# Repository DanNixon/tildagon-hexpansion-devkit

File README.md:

# Tildagon Hexpansion dev kit

A basic, quick and dirty development kit for hexpansions for the [Tildagon](https://tildagon.badge.emfcamp.org/) badge.

Accurately replicates i2c and low speed IO/LED drivers of ports D, E and F from the actual badge, with breakouts for the entire expansion port.
i2c is as per the actual badge, with the AW9523B connected to port 7 of the TCA9548A.
Default address configuration of both the AW9523B and TCA9548A match what is used on the badge (so you should not have to adjust the solder jumpers).

Paired with your ESP32-S3 dev board of choice, this should allow you to develop something more than "shape with LED" hexpansions prior to EMF 2024.

## Pinouts

"Pin" refers to the index used on the Tildagon design files.
"Letter" refers to the letter assigned to the pins in the Hexpansion example.
Why the two different pin identification schemes exist is a mystery to me...

### Low Speed

| Pin | Letter | Port D | Port E | Port F |
|-----|--------|--------|--------|--------|
| 1   | A      | 1.0    | 0.2    | 0.7    |
| 2   | B      | 1.1    | 0.3    | 1.4    |
| 3   | C      | 1.2    | 0.4    | 1.5    |
| 4   | D      | 1.3    | 0.5    | 1.6    |
| 5   | E      | 0.0    | 0.6    | 1.7    |

### High Speed

| Pin | Letter |
|-----|--------|
| 1   | F      |
| 2   | G      |
| 3   | H      |
| 4   | I      |

### i2c

| Bus | Port |
|-----|------|
| 4   | D    |
| 5   | E    |
| 6   | F    |
| 7   | sys  |

## See also

- [badge-2024-hardware](https://github.com/emfcamp/badge-2024-hardware)
- [TCA9548A datasheet](https://www.ti.com/lit/ds/symlink/tca9548a.pdf)
- [AW9523B datasheet](https://cdn-shop.adafruit.com/product-files/4886/AW9523+English+Datasheet.pdf)
- [Hexpansion developer guide](https://tildagon.badge.emfcamp.org/technical-reference/hexpansions/)

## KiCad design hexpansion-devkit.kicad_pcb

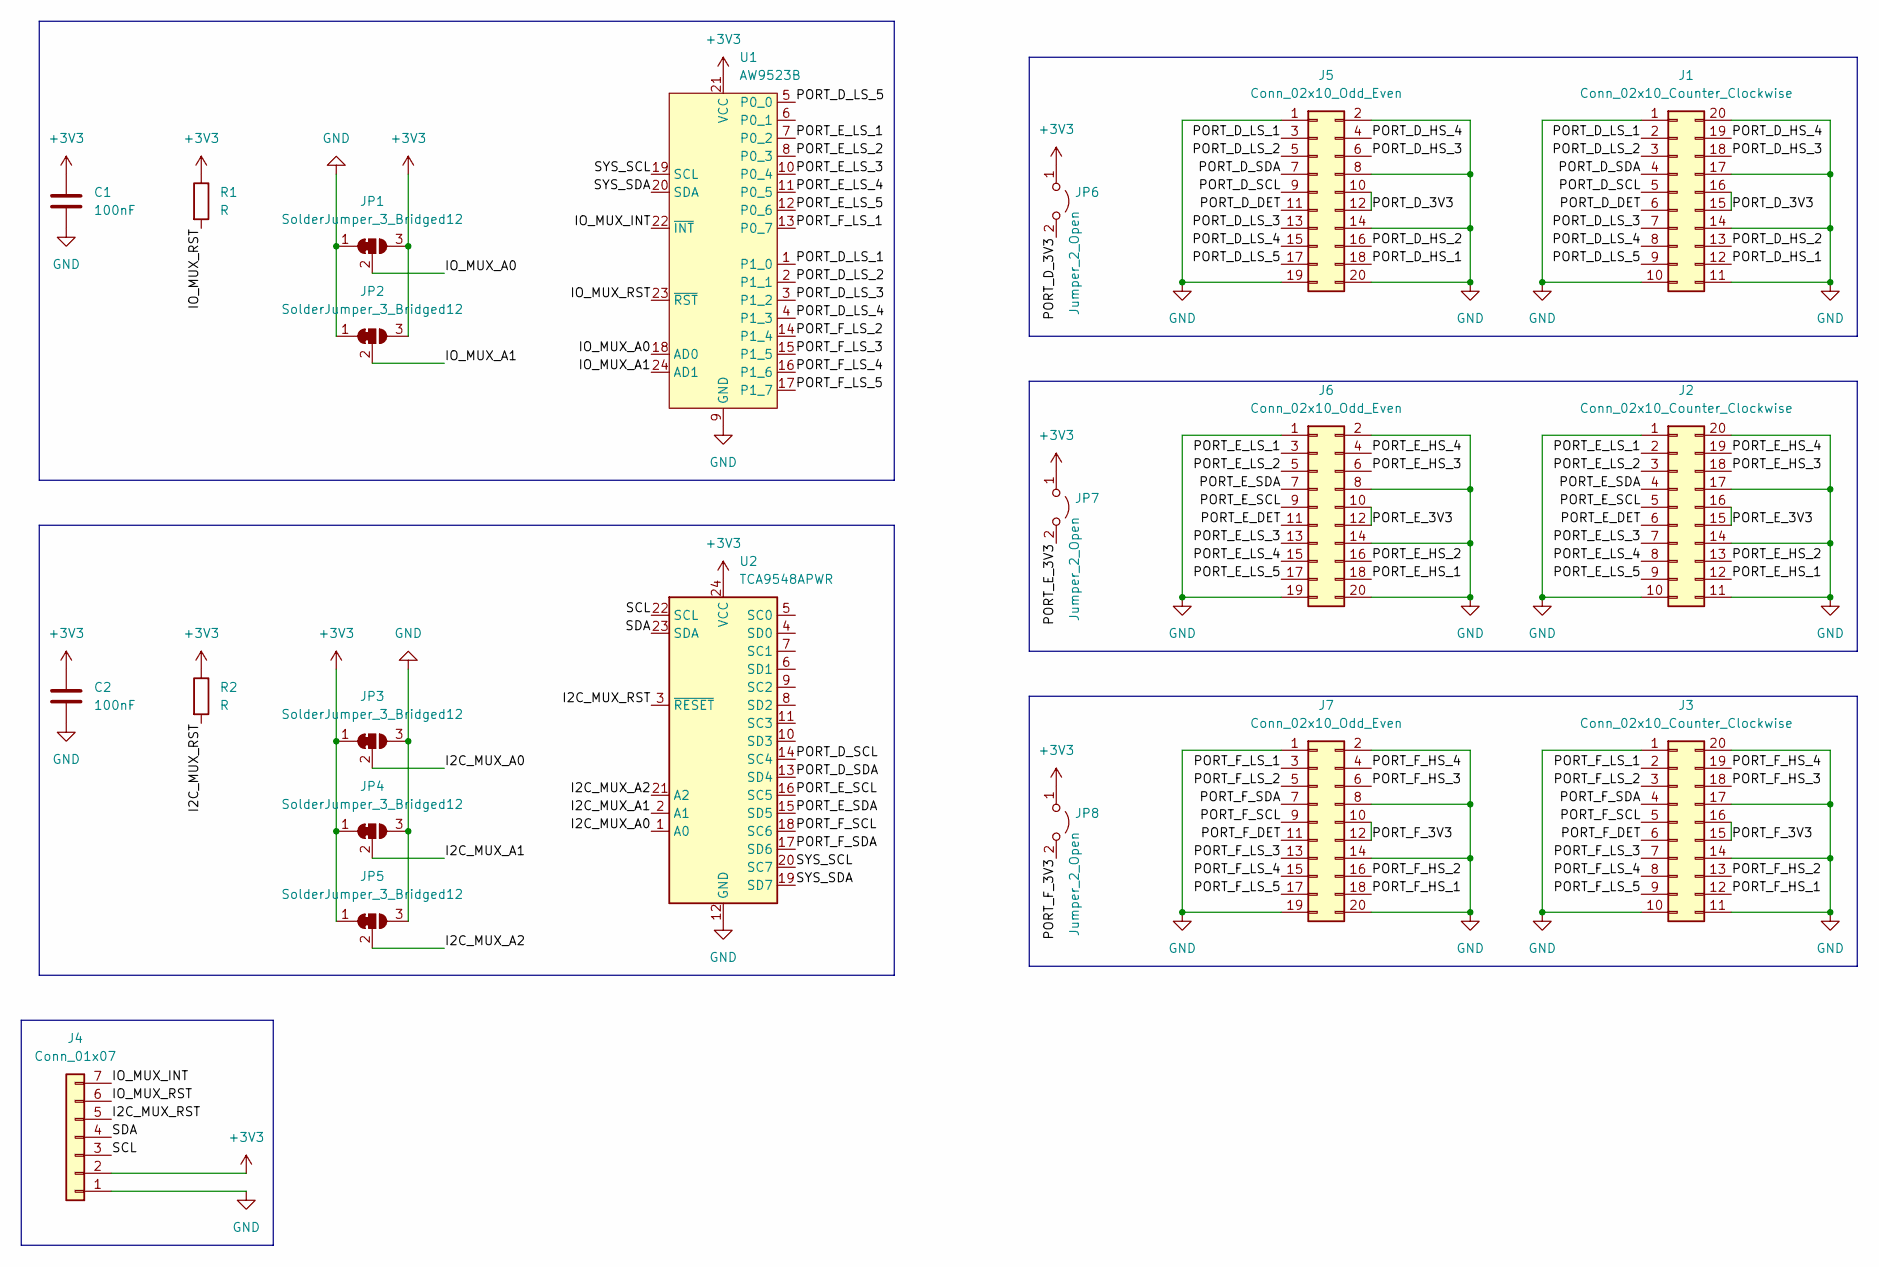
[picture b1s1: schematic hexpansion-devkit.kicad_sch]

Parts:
C1, C2: 100nF; C_0603_1608Metric; LCSC C497032
J1, J2, J3: Conn_02x10_Counter_Clockwise; SFP; LCSC C2897291
J4: Conn_01x07; PinHeader_1x07_P2.54mm_Vertical
J5, J6, J7: Conn_02x10_Odd_Even; PinHeader_2x10_P2.54mm_Vertical
JP1, JP2, JP3, JP4, JP5: SolderJumper_3_Bridged12; SolderJumper-3_P1.3mm_Bridged12_RoundedPad1.0x1.5mm
JP6, JP7, JP8: Jumper_2_Open; TestPoint_2Pads_Pitch2.54mm_Drill0.8mm
R1, R2: R; R_0603_1608Metric; LCSC C2907127
U1: AW9523B; QFN-24-1EP_4x4mm_P0.5mm_EP2.7x2.6mm; LCSC C148077
U2: TCA9548APWR; TSSOP-24_4.4x7.8mm_P0.65mm; LCSC C130026

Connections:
+3V3: C1.1, C2.1, J4.2, JP1.3 (B), JP2.3 (B), JP3.1 (A), JP4.1 (A), JP5.1 (A), JP6.1 (A), JP7.1 (A), JP8.1 (A), R1.1, R2.1, U1.21 (VCC), U2.24 (VCC)
/I2C_MUX_A0: JP3.2 (C), U2.1 (A0)
/I2C_MUX_A1: JP4.2 (C), U2.2 (A1)
/I2C_MUX_A2: JP5.2 (C), U2.21 (A2)
/I2C_MUX_RST: J4.5, R2.2, U2.3 (~RESET)
/IO_MUX_A0: JP1.2 (C), U1.18 (AD0)
/IO_MUX_A1: JP2.2 (C), U1.24 (AD1)
/IO_MUX_INT: J4.7, U1.22 (~INT)
/IO_MUX_RST: J4.6, R1.2, U1.23 (~RST)
/PORT_D_3V3: J1.15, J1.16, J5.10, J5.12, JP6.2 (B)
/PORT_D_DET: J1.6, J5.11
/PORT_D_HS_1: J1.12, J5.18
/PORT_D_HS_2: J1.13, J5.16
/PORT_D_HS_3: J1.18, J5.6
/PORT_D_HS_4: J1.19, J5.4
/PORT_D_LS_1: J1.2, J5.3, U1.1 (P1_0)
/PORT_D_LS_2: J1.3, J5.5, U1.2 (P1_1)
/PORT_D_LS_3: J1.7, J5.13, U1.3 (P1_2)
/PORT_D_LS_4: J1.8, J5.15, U1.4 (P1_3)
/PORT_D_LS_5: J1.9, J5.17, U1.5 (P0_0)
/PORT_D_SCL: J1.5, J5.9, U2.14 (SC4)
/PORT_D_SDA: J1.4, J5.7, U2.13 (SD4)
/PORT_E_3V3: J2.15, J2.16, J6.10, J6.12, JP7.2 (B)
/PORT_E_DET: J2.6, J6.11
/PORT_E_HS_1: J2.12, J6.18
/PORT_E_HS_2: J2.13, J6.16
/PORT_E_HS_3: J2.18, J6.6
/PORT_E_HS_4: J2.19, J6.4
/PORT_E_LS_1: J2.2, J6.3, U1.7 (P0_2)
/PORT_E_LS_2: J2.3, J6.5, U1.8 (P0_3)
/PORT_E_LS_3: J2.7, J6.13, U1.10 (P0_4)
/PORT_E_LS_4: J2.8, J6.15, U1.11 (P0_5)
/PORT_E_LS_5: J2.9, J6.17, U1.12 (P0_6)
/PORT_E_SCL: J2.5, J6.9, U2.16 (SC5)
/PORT_E_SDA: J2.4, J6.7, U2.15 (SD5)
/PORT_F_3V3: J3.15, J3.16, J7.10, J7.12, JP8.2 (B)
/PORT_F_DET: J3.6, J7.11
/PORT_F_HS_1: J3.12, J7.18
/PORT_F_HS_2: J3.13, J7.16
/PORT_F_HS_3: J3.18, J7.6
/PORT_F_HS_4: J3.19, J7.4
/PORT_F_LS_1: J3.2, J7.3, U1.13 (P0_7)
/PORT_F_LS_2: J3.3, J7.5, U1.14 (P1_4)
/PORT_F_LS_3: J3.7, J7.13, U1.15 (P1_5)
/PORT_F_LS_4: J3.8, J7.15, U1.16 (P1_6)
/PORT_F_LS_5: J3.9, J7.17, U1.17 (P1_7)
/PORT_F_SCL: J3.5, J7.9, U2.18 (SC6)
/PORT_F_SDA: J3.4, J7.7, U2.17 (SD6)
/SCL: J4.3, U2.22 (SCL)
/SDA: J4.4, U2.23 (SDA)
/SYS_SCL: U1.19 (SCL), U2.20 (SC7)
/SYS_SDA: U1.20 (SDA), U2.19 (SD7)
GND: C1.2, C2.2, J1.1, J1.10, J1.11, J1.14, J1.17, J1.20, J2.1, J2.10, J2.11, J2.14, J2.17, J2.20, J3.1, J3.10, J3.11, J3.14, J3.17, J3.20, J4.1, J5.1, J5.2, J5.8, J5.14, J5.19, J5.20, J6.1, J6.2, J6.8, J6.14, J6.19, J6.20, J7.1, J7.2, J7.8, J7.14, J7.19, J7.20, JP1.1 (A), JP2.1 (A), JP3.3 (B), JP4.3 (B), JP5.3 (B), U1.9 (GND), U1.25 (GND), U2.12 (GND)

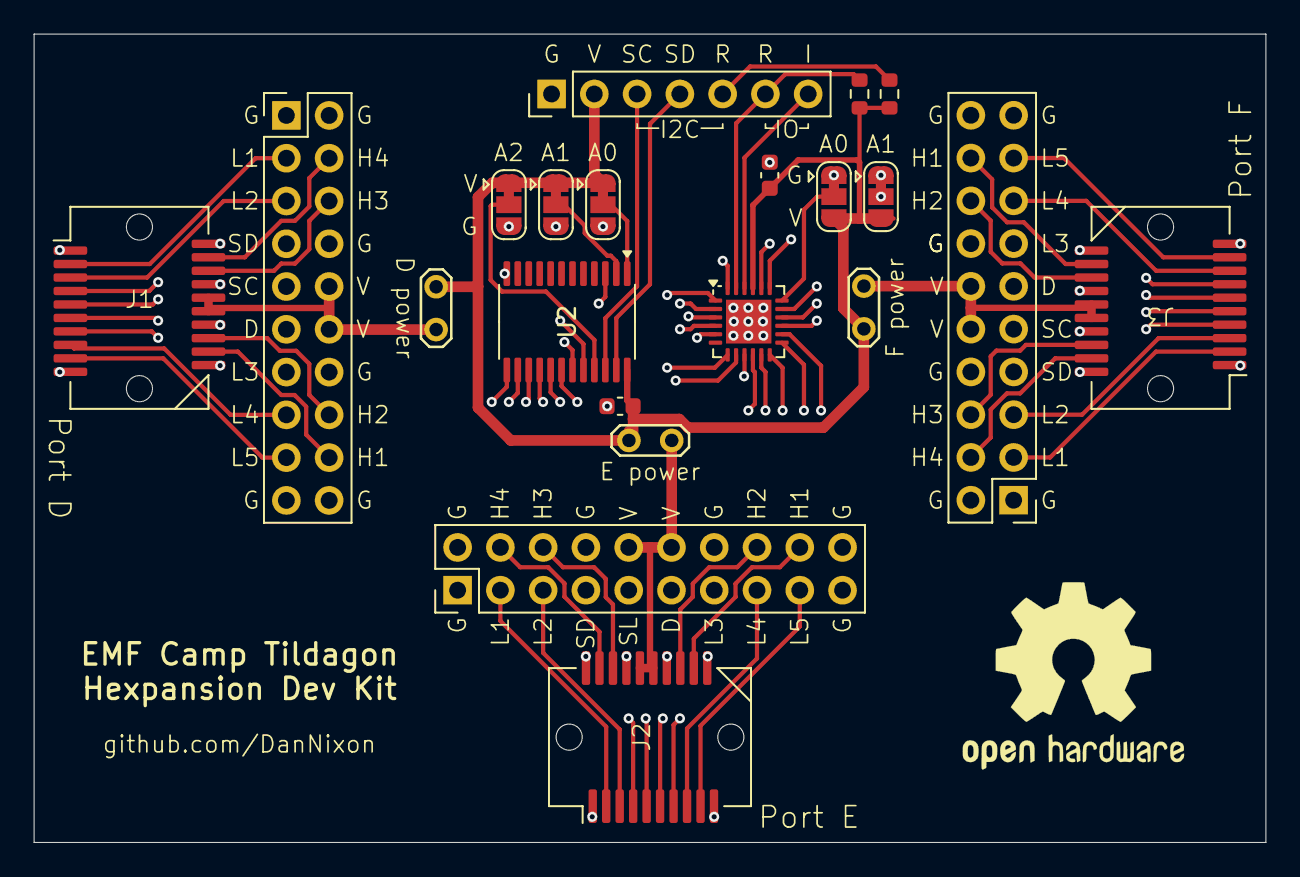
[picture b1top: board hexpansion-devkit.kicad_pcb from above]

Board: 4 copper layers, 73.2 x 48.0 mm, 21 parts (0 on the bottom side), 53 nets.

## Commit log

2024-03-25 Revision 1
2024-04-03 Revision 2
2024-04-03 Move PCB files to subdir
2024-04-03 Test programs
2024-04-03 Flake, formatting and CI
2024-04-03 Docs
2024-04-03 Remove stray notes
2024-04-08 Tidy PCB silkscreen, add new render
2024-04-22 Add FUNDING.yml
2024-04-29 Add pinouts
2024-04-29 Test program for rabbit, blue duck and MS badge hexpansions
2024-05-01 Add MS hexpansion breathe effect
2024-05-13 Bump DeterminateSystems/nix-installer-action from 10 to 11
    Bumps [DeterminateSystems/nix-installer-action](https://github.com/determinatesystems/nix-installer-action) from 10 to 11.
    - [Release notes](https://github.com/determinatesystems/nix-installer-action/releases)
    - [Commits](https://github.com/determinatesystems/nix-installer-action/compare/v10...v11)
    ---
    updated-dependencies:
    - dependency-name: DeterminateSystems/nix-installer-action
2024-05-14 More Maker Space M testing
2024-06-10 Bump DeterminateSystems/nix-installer-action from 11 to 12
    Bumps [DeterminateSystems/nix-installer-action](https://github.com/determinatesystems/nix-installer-action) from 11 to 12.
    - [Release notes](https://github.com/determinatesystems/nix-installer-action/releases)
    - [Commits](https://github.com/determinatesystems/nix-installer-action/compare/v11...v12)
    ---
    updated-dependencies:
    - dependency-name: DeterminateSystems/nix-installer-action
2024-07-29 Bump DeterminateSystems/nix-installer-action from 12 to 13
    Bumps [DeterminateSystems/nix-installer-action](https://github.com/determinatesystems/nix-installer-action) from 12 to 13.
    - [Release notes](https://github.com/determinatesystems/nix-installer-action/releases)
    - [Commits](https://github.com/determinatesystems/nix-installer-action/compare/v12...v13)
    ---
    updated-dependencies:
    - dependency-name: DeterminateSystems/nix-installer-action
2024-09-16 Bump DeterminateSystems/nix-installer-action from 13 to 14
    Bumps [DeterminateSystems/nix-installer-action](https://github.com/determinatesystems/nix-installer-action) from 13 to 14.
    - [Release notes](https://github.com/determinatesystems/nix-installer-action/releases)
    - [Commits](https://github.com/determinatesystems/nix-installer-action/compare/v13...v14)
    ---
    updated-dependencies:
    - dependency-name: DeterminateSystems/nix-installer-action
2024-11-11 Bump DeterminateSystems/nix-installer-action from 14 to 15
    Bumps [DeterminateSystems/nix-installer-action](https://github.com/determinatesystems/nix-installer-action) from 14 to 15.
    - [Release notes](https://github.com/determinatesystems/nix-installer-action/releases)
    - [Commits](https://github.com/determinatesystems/nix-installer-action/compare/v14...v15)
    ---
    updated-dependencies:
    - dependency-name: DeterminateSystems/nix-installer-action
2024-11-18 Bump DeterminateSystems/nix-installer-action from 15 to 16
    Bumps [DeterminateSystems/nix-installer-action](https://github.com/determinatesystems/nix-installer-action) from 15 to 16.
    - [Release notes](https://github.com/determinatesystems/nix-installer-action/releases)
    - [Commits](https://github.com/determinatesystems/nix-installer-action/compare/v15...v16)
    ---
    updated-dependencies:
    - dependency-name: DeterminateSystems/nix-installer-action
2025-04-28 Bump DeterminateSystems/nix-installer-action from 16 to 17
    Bumps [DeterminateSystems/nix-installer-action](https://github.com/determinatesystems/nix-installer-action) from 16 to 17.
    - [Release notes](https://github.com/determinatesystems/nix-installer-action/releases)
    - [Commits](https://github.com/determinatesystems/nix-installer-action/compare/v16...v17)
    ---
    updated-dependencies:
    - dependency-name: DeterminateSystems/nix-installer-action
2025-07-07 Bump DeterminateSystems/nix-installer-action from 17 to 18
    Bumps [DeterminateSystems/nix-installer-action](https://github.com/determinatesystems/nix-installer-action) from 17 to 18.
    - [Release notes](https://github.com/determinatesystems/nix-installer-action/releases)
    - [Commits](https://github.com/determinatesystems/nix-installer-action/compare/v17...v18)
    ---
    updated-dependencies:
    - dependency-name: DeterminateSystems/nix-installer-action
